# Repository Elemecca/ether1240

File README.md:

# Ethernet Comm Pack for Tektronix 1240

This project is a Comm Pack for the Tektronix 1240 and 1241 logic
analyzers that provides a few interface options:

- [LXI]<sup>&reg;</sup>-compatible<sup><a name="ref1" href="#user-content-note1">1</a></sup> Ethernet
- USB serial (CDC)
- RS-232 serial over DB-9

[LXI]: http://www.lxistandard.org/About/AboutLXI.aspx

## Copyright and License

All files in this repository (with the exception of third-party
documentation under `/docs/datasheets/` and ROM images in `/reverse/`)
are copyright 2017 Sam Hanes.

The documentation under `/docs/` (with the exception of third-party
documentation under `/docs/datasheets/`) is licensed under the
[Creative Commons Attribution-ShareAlike 4.0 International License][CC]
(CC-BY-SA). See `/docs/README.md` for details and `/docs/LICENSE.txt`
for the full license text.

[CC]: https://creativecommons.org/licenses/by-sa/4.0/

The hardware design documentation under `/hardware/` is licensed under
the [CERN Open Hardware Licence][OHL] version 1.2 or newer.
See `/hardware/README.md` for details and `/hardware/LICENSE.txt` for
the full license text.

[OHL]: https://www.ohwr.org/projects/cernohl/wiki/cernohl

<a name="note1" href="#user-content-ref1">Note 1</a>:
LXI<sup>&reg;</sup> is a registered trademark of the LXI Consortium.
This project is not certified by the LXI Consortium. Our use of the
LXI<sup>&reg;</sup> trademark is solely to identify the standard with
which we attempt to comply and should not be taken to imply any
endorsement of this project or its creators by the LXI Consortium.

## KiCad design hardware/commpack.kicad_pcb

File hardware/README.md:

This directory contains the hardware design documentation for the
Ether1240 project. The Schematic and PCB designs are maintained with
the open source [KiCad] EDA package.

[KiCad]: http://kicad-pcb.org/

### Backup ROM Socket

As a backup to the bus controller's ROM emulation, the device has a
15.24mm DIP-28 socket that accepts ROMs compatible with the Intel 27128
EPROM used on the original comm packs. In-circuit programming is
supported for the Atmel AT28C64B and AT28C256 parallel EEPROMs, but only
when the device is disconnected from the 1240 and running on USB power.

## Copyright and License

Copyright 2017 Sam Hanes

This documentation describes Open Hardware and is licensed under the
CERN OHL v1.2.

You may redistribute and modify this documentation under the terms of
the [CERN OHL v.1.2][OHL]. This documentation is distributed WITHOUT ANY
EXPRESS OR IMPLIED WARRANTY, INCLUDING OF MERCHANTABILITY, SATISFACTORY
QUALITY AND FITNESS FOR A PARTICULAR PURPOSE. Please see the CERN OHL
v1.2 for applicable conditions. You should have received a copy of the
OHL alonside this documentation in the file `LICENSE.txt`.

[OHL]: https://www.ohwr.org/projects/cernohl/wiki/cernohl

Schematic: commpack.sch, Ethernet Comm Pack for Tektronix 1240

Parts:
A1: Omega2+; Omega2
C1, C2, C3, C4, C5: 22u; C_0805_HandSoldering
C6, C7: 47p; C_0805_HandSoldering
H1, H2, H3, H4: Mount; MountingHole_140mil_Pad
J1: 1240COMM
J3: L8BE-1G1T-91A
J4: USB_B
R1, R2: 27R; R_2010_HandSoldering
R3: 4k7; R_2010_HandSoldering
R4: 10k; R_2010_HandSoldering
U1: SC16C550B; LQFP-48_7x7mm_Pitch0.5mm
U2: SST39SF010A; PLCC-32_THT-Socket
U3: HCF4010; SOIC-16_3.9x9.9mm_Pitch1.27mm
U4: AP1117-33; SOT-223-3_TabPin2
U5: FT230XS; SSOP-16_3.9x4.9mm_Pitch0.635mm
Y1: 22.1184M; Crystal_HC49-U_Vertical

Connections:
+3V3: A1.B2, C3.1, U3.1, U4.2 (VO), U5.3, U5.10, U5.11, U5.12
/A-RX: A1.A8, U3.4
/A-TX: A1.A9, U1.7
/A-~CTS: A1.A7, U3.2
/A-~RTS: A1.A6, U1.38
/E-LED1: A1.B13, J3.14
/E-LED2: A1.B14, J3.16
/E-RX+: A1.B12, J3.4
/E-RX-: A1.B11, J3.6
/E-TX+: A1.B10, J3.12
/E-TX-: A1.B9, J3.10
/H-A0: J1.A16 (A0), U1.28, U2.12
/H-A1: J1.B1 (A1), U1.27, U2.11
/H-A2: J1.A17 (A2), U1.26, U2.10
/H-A3: J1.B2 (A3), U2.9
/H-A4: J1.A18 (A4), U2.8
/H-A5: J1.A3 (A5), U2.7
/H-A6: J1.B16 (A6), U2.6
/H-A7: J1.B4 (A7), U2.5
/H-A8: J1.B15 (A8), U2.27
/H-A9: J1.B5 (A9), U2.26
/H-A10: J1.B14 (A10), U2.23
/H-A11: J1.B6 (A11), U2.25
/H-A12: J1.B13 (A12), U2.4
/H-A13: J1.B7 (A13), U2.28
/H-D0: J1.A11 (D0), U1.43, U2.13
/H-D1: J1.A4 (D1), U1.44, U2.14
/H-D2: J1.A10 (D2), U1.45, U2.15
/H-D3: J1.A5 (D3), U1.46, U2.17
/H-D4: J1.A9 (D4), U1.47, U2.18
/H-D5: J1.A6 (D5), U1.2, U2.19
/H-D6: J1.A8 (D6), U1.3, U2.20
/H-D7: J1.A7 (D7), U1.4, U2.21
/H-INT: J1.A14 (INT), U1.30
/H-RST: J1.A2 (RESET), U1.35
/H-~CS: J1.B3 (~COMM), U1.11
/H-~RD: J1.A15 (~RD), U1.19, U2.24
/H-~RS: J1.A13 (~CROM), U2.22
/H-~WR: J1.A1 (~WR), U1.16, U2.31
/R-A14: U1.33, U2.29
/R-A15: U1.34, U2.3
/R-A16: U1.31, U2.2
/U-TX: U1.8, U3.5
/U-~RTS: U1.32, U3.3
Earth_Protective: H1.1, H2.1, H3.1, H4.1, J1.B11 (SGND), J3.17, J3.18, J3.19, J3.20
GND: A1.A1, A1.B1, C1.2, C2.2, C3.2, C4.2, C5.2, C6.2, C7.2, J1.A20 (GND), J1.B20 (GND), J3.13, J3.15, R4.2, U1.9, U1.10, U1.17, U1.18, U1.20, U1.24, U2.16, U3.8, U4.1 (GND), U5.5, U5.13
unnamed: A1.B5, U5.1
unnamed: A1.B6, U5.4
unnamed: C1.1, U1.14, Y1.1
unnamed: C2.1, U1.15, Y1.2
unnamed: C6.1, R2.1
unnamed: C7.1, R1.1
unnamed: R1.2, U5.9
unnamed: R2.2, U5.8
unnamed: R3.2, R4.1, U5.15
unnamed: U1.5, U1.12

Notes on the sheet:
Host Bus Connector
Power
UART
Flash ROM
Ethernet
USB UART

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
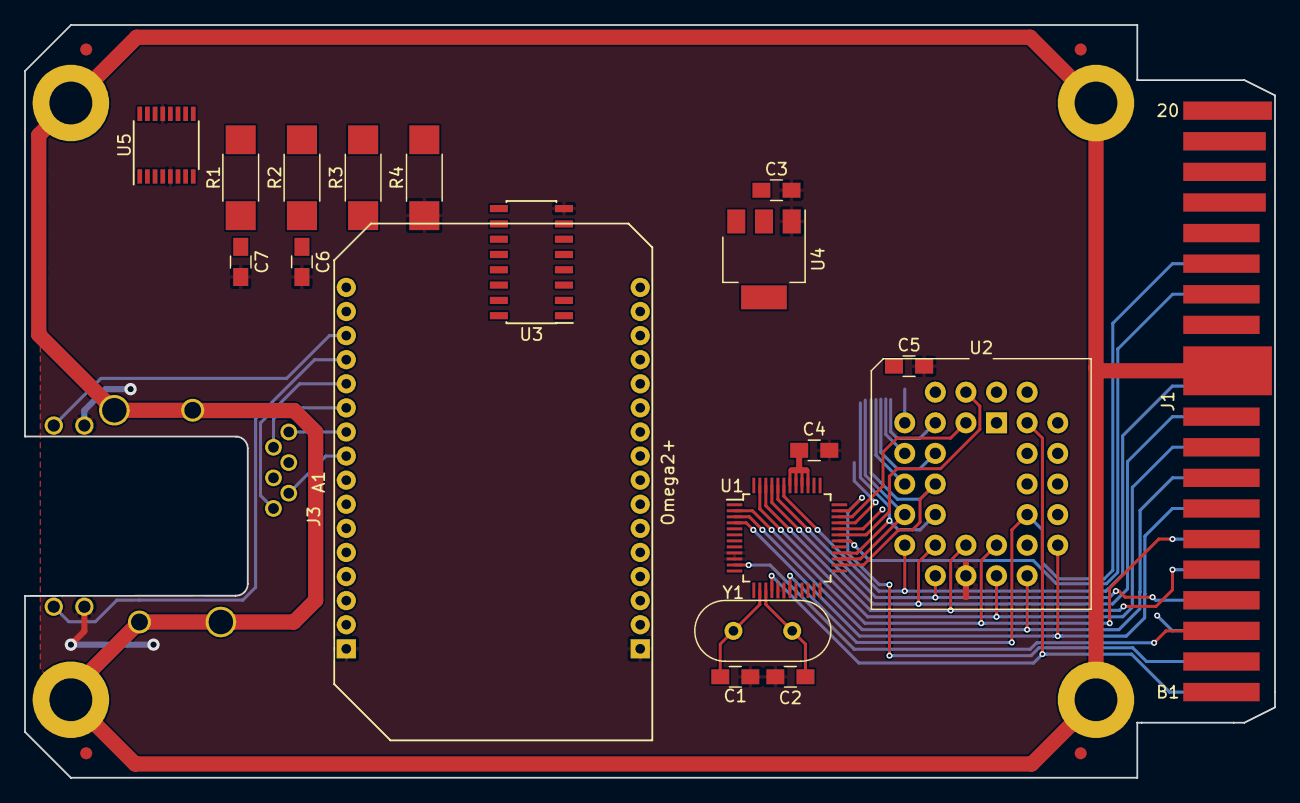
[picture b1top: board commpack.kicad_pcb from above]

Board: 2 copper layers, 103.8 x 62.5 mm, 29 parts (0 on the bottom side), 57 nets.

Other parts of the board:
Bonsai: Bonsai
FD1, FD2, FD3, FD4: Fiducial_1mm_Dia_2mm_Outer

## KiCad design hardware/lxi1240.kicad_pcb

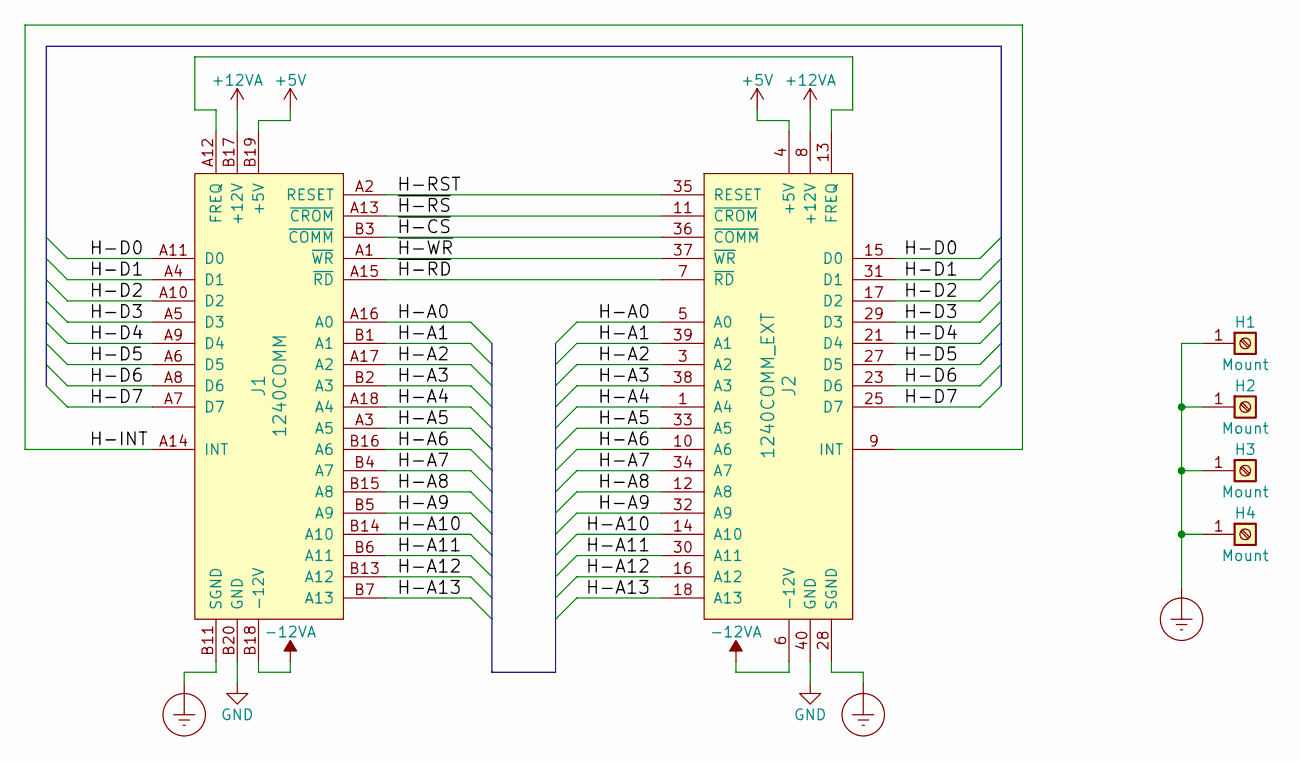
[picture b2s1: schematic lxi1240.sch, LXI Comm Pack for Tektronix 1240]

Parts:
H1, H2, H3, H4: Mount; MountingHole_140mil_Pad
J1: 1240COMM
J2: 1240COMM_EXT; ATA_HEADER

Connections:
+5V: J1.A19 (+5V), J1.B19 (+5V), J2.4 (+5V)
+12VA: J1.B17 (+12V), J2.8 (+12V)
-12VA: J1.B18 (-12V), J2.6 (-12V)
/H-A0: J1.A16 (A0), J2.5 (A0)
/H-A1: J1.B1 (A1), J2.39 (A1)
/H-A2: J1.A17 (A2), J2.3 (A2)
/H-A3: J1.B2 (A3), J2.38 (A3)
/H-A4: J1.A18 (A4), J2.1 (A4)
/H-A5: J1.A3 (A5), J2.33 (A5)
/H-A6: J1.B16 (A6), J2.10 (A6)
/H-A7: J1.B4 (A7), J2.34 (A7)
/H-A8: J1.B15 (A8), J2.12 (A8)
/H-A9: J1.B5 (A9), J2.32 (A9)
/H-A10: J1.B14 (A10), J2.14 (A10)
/H-A11: J1.B6 (A11), J2.30 (A11)
/H-A12: J1.B13 (A12), J2.16 (A12)
/H-A13: J1.B7 (A13), J2.18 (A13)
/H-D0: J1.A11 (D0), J2.15 (D0)
/H-D1: J1.A4 (D1), J2.31 (D1)
/H-D2: J1.A10 (D2), J2.17 (D2)
/H-D3: J1.A5 (D3), J2.29 (D3)
/H-D4: J1.A9 (D4), J2.21 (D4)
/H-D5: J1.A6 (D5), J2.27 (D5)
/H-D6: J1.A8 (D6), J2.23 (D6)
/H-D7: J1.A7 (D7), J2.25 (D7)
/H-INT: J1.A14 (INT), J2.9 (INT)
/H-RST: J1.A2 (RESET), J2.35 (RESET)
/~H-CS: J1.B3 (~COMM), J2.36 (~COMM)
/~H-RD: J1.A15 (~RD), J2.7 (~RD)
/~H-RS: J1.A13 (~CROM), J2.11 (~CROM)
/~H-WR: J1.A1 (~WR), J2.37 (~WR)
Earth_Protective: H1.1, H2.1, H3.1, H4.1, J1.B11 (SGND), J2.28 (SGND)
GND: J1.A20 (GND), J1.B20 (GND), J2.2 (GND), J2.19 (GND), J2.22 (GND), J2.24 (GND), J2.26 (GND), J2.40 (GND)
unnamed: J1.A12 (FREQ), J2.13 (FREQ)

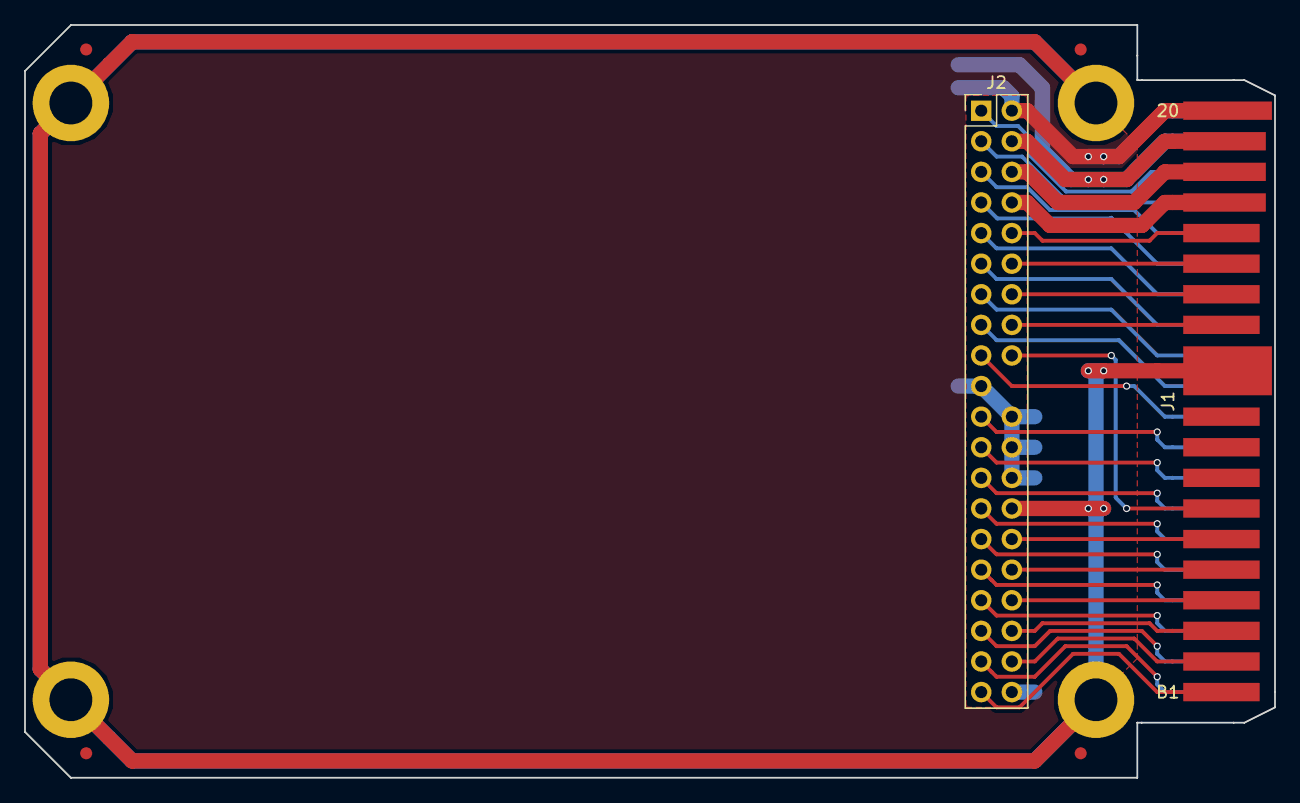
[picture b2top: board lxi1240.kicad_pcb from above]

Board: 2 copper layers, 103.8 x 62.5 mm, 11 parts (0 on the bottom side), 34 nets.

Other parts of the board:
Bonsai: Bonsai
FD1, FD2, FD3, FD4: Fiducial_1mm_Dia_2mm_Outer

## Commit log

2017-11-04 Set up basic board outline and card edge connector.
2017-11-05 Make board-edge symbol compliant with KLC.
2017-11-05 Add a breakout header for the board edge connector.
2017-11-05 Add mounting holes with protective ground.
2017-11-05 Add ground pours.
2017-11-05 Remove pad for key pin in ATA header.
2017-11-05 Shorten ground paths.
2017-11-05 Move PE to ATA pin 28 so slave connector is usable.
2017-11-05 Add fiducials and chamfer corners.
2017-11-05 Add CERN OHL license notices.
2017-11-08 Update board for more accurate measurements of the original.
2017-11-08 Move ATA header closer to board edge.
2017-11-08 Add a PIC micro to manage the host bus.
2017-11-08 Install Git LFS for datasheet PDFs.
2017-11-17 Begin analysis of host bus timings.
2017-11-17 Start building enclosure in OpenSCAD.
2017-11-17 enclosure: center box and use slope instead of inset.
2017-11-21 Add note about use of LXI trademark.
2017-11-21 Add CC-BY-SA license for docs.
2017-11-21 Rename project files to remove LXI mark.
2017-11-21 Build footprint for MagJack.
2017-11-21 Remove PIC16, add Ethernet port to schematic, fix SGND.
    The PIC16 micro isn't fast enough to perform reliable bus emulation.
2017-11-21 Add USB-B connector.
2017-11-21 Add ground pour over card-edge connector.
2017-11-21 Add 27128 socket to PCB and route it.
2017-11-22 Make routing for ROM socket more compact.
2017-11-23 Some progress on bus timings.
2017-11-23 Duplicate trace cleanup on export.
2017-11-30 Add Omega2 footprint to board.
2017-11-30 Reroute traces under 27C128 socket again.
2017-12-03 Change ATA pinout, rip up EPROM socket and Omega2.
    I missed two grounded pins when I did the original ATA connector pinout,
    so this drops the +12V and -12V connections and rearranges everything to
    avoid shorting two of the address lines to ground.
2017-12-04 Clean up routing from card edge to ATA connector.
2019-07-21 Add reverse engineering working files.
2019-07-21 Update schematic to KiCAD 5.0.
2019-07-21 Reduce mask expansion to get fingers between UART pads.
2019-07-21 Add a level shifter on the serial lines to the Omega2.
2019-07-21 Fix up rear silkscreen.
2019-07-21 Clean up track with and spacing.
2019-07-21 Fix alignment of crystal traces.
2019-07-21 Add decoupling caps on UART and ROM.
2019-07-21 Add UART, flash ROM to schematic.
2019-07-21 Clean up ground planes a bit.
2019-07-21 Place UART and ROM, route data bus.
2019-07-21 Route the remaining signals.
2019-07-21 Fix via size on power traces.
2019-07-21 Convert level shifter symbol to multi-unit.
2019-07-21 Switch Y1 to through-hole footprint.
2019-07-21 Rename local libraries.
2019-07-21 Some WIP on the UART board.
    I don't actually know what changed; this was months ago.
2019-07-21 Add ROMs to Ghidra project.
2019-07-22 Begin disassembling, fix DROM location.
2019-07-22 Add IO memory map, label most IO.
2019-07-25 RE IOP RAM test sequence.
2019-07-28 RE most of ROM test code.

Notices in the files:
hardware/commpack.kicad_pcb:
© 2017 Sam Hanes
Licensed under CERN OHL v1.2 or newer
hardware/commpack.sch:
Licensed under CERN OHL v1.2 or later
